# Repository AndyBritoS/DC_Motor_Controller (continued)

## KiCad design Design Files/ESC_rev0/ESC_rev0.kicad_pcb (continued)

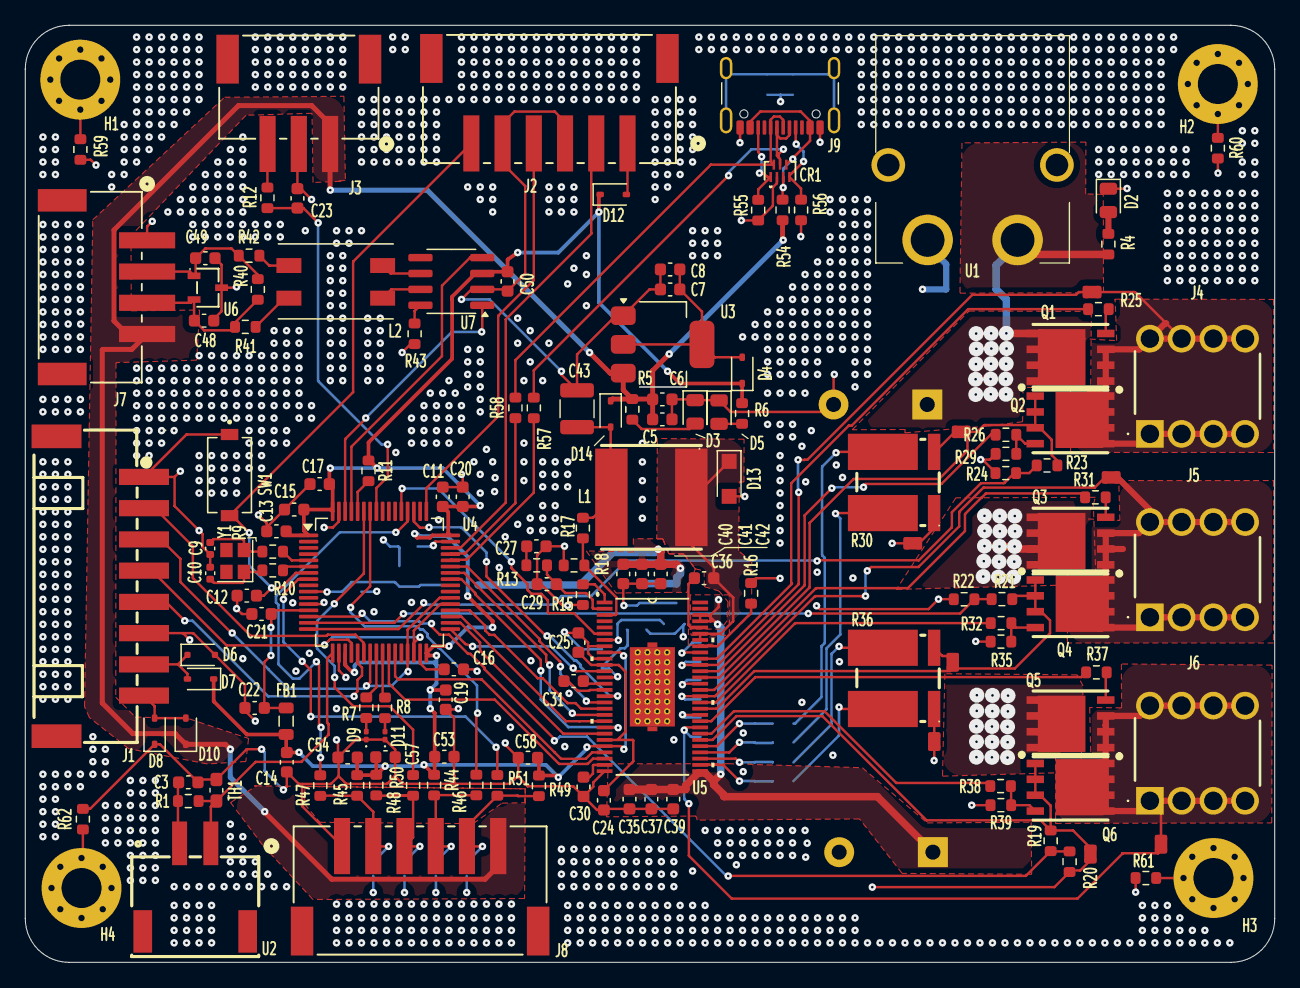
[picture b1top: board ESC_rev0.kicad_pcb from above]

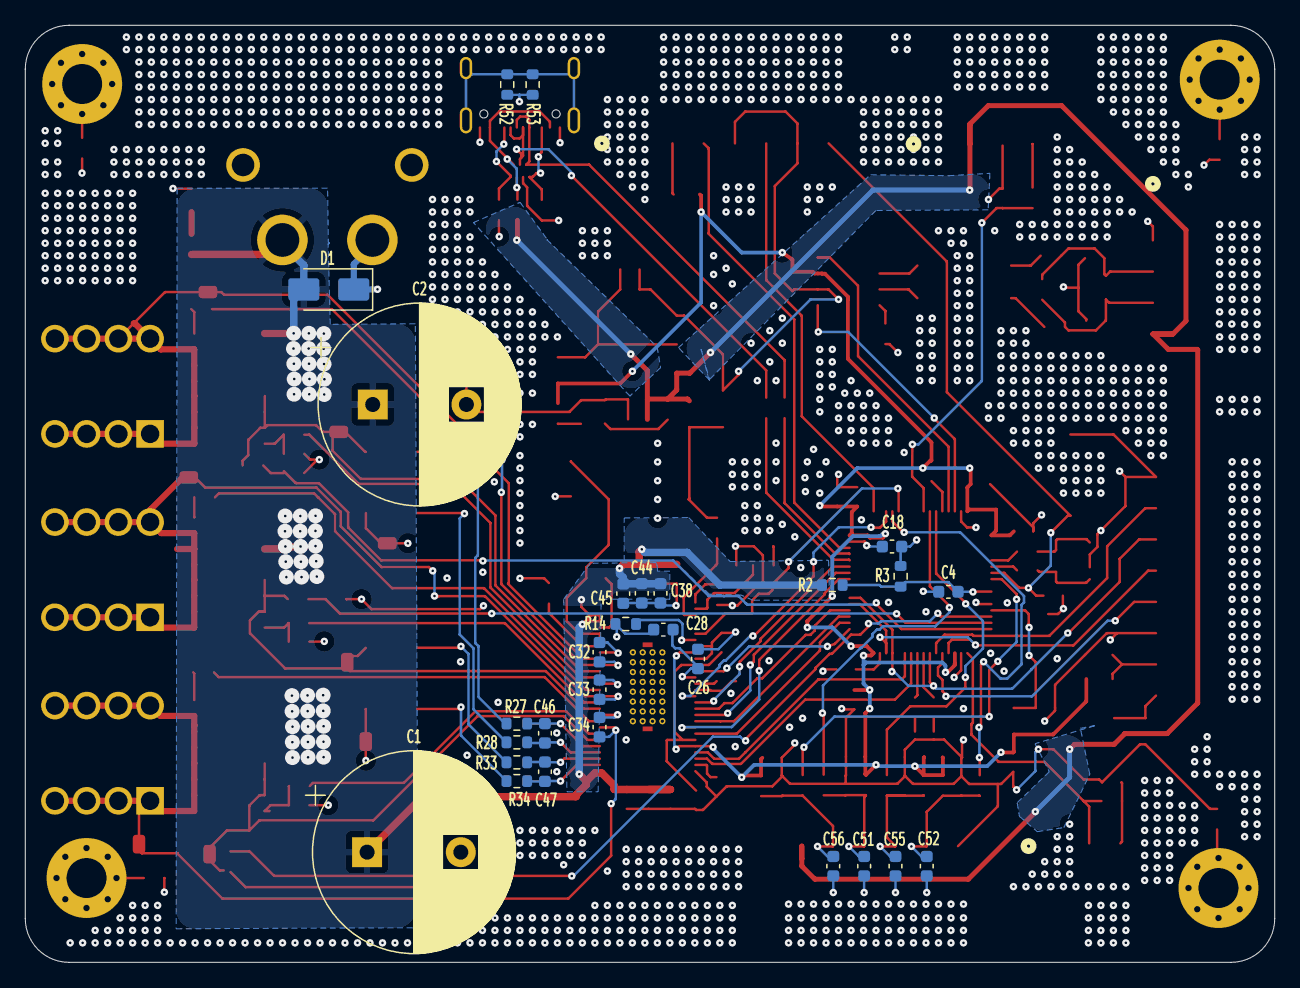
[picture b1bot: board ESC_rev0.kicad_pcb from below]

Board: 4 copper layers, 100.0 x 75.0 mm, 175 parts (28 on the bottom side), 128 nets.

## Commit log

2024-12-27 Update1
    Created kicad project and block diagram on schematics
2024-12-28 update2
    MCU sch
2024-12-29 update3
    Added DRV8302 footprint and started the Mosfet driver schematic.
2025-01-03 update4
    gate driver left side complete
2025-01-04 update 5
    gate driver right side
2025-01-05 update 6
    gate driver completion and mosfet init
2025-01-05 update 7
    mosfet page completion
2025-01-06 update 8
    conclusion of mosfets and input protection; can almost concluded
2025-01-07 update 9
    filters and USB complete
2025-01-07 update10
    modifications to root page, completion of pages step_down and mechanical
2025-01-07 update11
    root page base complete
2025-01-08 UPDATE 12
    started schematics revision: edit and added info and circuits to some pages and assigned some footprints for components
2025-01-17 update 13
    assigned all footprints (provisionally) and imported them - errors and warning occurred, must be corrected in the future
2025-01-18 update 14
    Circuits separated by schematic pages. Replaced crystal footprint.
2025-01-20 update 15
    Simple connectors replaced by smd connectors (downloaded). Connectors were placed in edges of the board.
2025-01-21 update 16
    All components placed on board. Some components modifications and addition were made: added 3D models, changed some symbols and footprints positions and some component types.
2025-01-22 update 17
    Defined board stackup, constraints and net classes for USB and CAN. Some components were slightly moved; shunt filters were place next do the gate driver pins. External calculators were used, check c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
2025-01-23 update 18
    Route process partially complete. Some corrections were made in footprints and pins references. Probably the power lines will need changes in size.
2025-01-23 update 19
    Preliminary routing finished, all signaling connections made.
2025-01-24 update 20
    Tracing complete (some power tracks need to be validated and some others optimizations weren't made). All connections were made, reference planes created, copper pour on mosfets and other power pads 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
2025-01-27 update 21
    DRC checked, all problems solved. Created Custom Rules to following JLCPCB most important capabilities. Relevant modifications on tracks, components positions and to copper pours were made. Board ima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
2025-01-27 update 22
    Board complete - not perfect for production, it is just a demo. Generated gerber files through extensions, prepared some layout infos, updated the schematics with images. Note: due to a power outage,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
